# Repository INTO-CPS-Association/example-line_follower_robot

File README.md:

# Line Follower Robot

## Overview
This example was originally developed in the DESTECS project. The model simulates a robot that can follow a line painted on the ground. The line contrasts from the background and the robot uses a number of sensors to detect light and dark areas on the ground. The robot has two wheels, each powered by individual motors to enable the robot to make controlled changes in direction. The number and position of the sensors may be configured in the model. A controller takes input from the sensors and encoders from the wheels to make outputs to the motors.

The robot moves through a number of phases as it follows a line. At the start of each line is a specific pattern that will be known in advance. Once a genuine line is detected on the ground, the robot follows it until it detects that the end of the line has been reached, when it should go to an idle state.

## Supported Features
This study supports the following INTO-CPS technologies:

* Multi-CT model
* 20-Sim (for FMU)
* OpenModelica (for FMU)
* VDM-RT (for FMU)
* INTO-CPS SysML  
* Co-simulation Engine (COE)
* Design Space Exploration
* Test Automation
* Model Checking
* Code Generation

## Additional Information
Additional Information about this case study can be found in the [Examples Compendium](http://projects.au.dk/fileadmin/D3.5_Examples_Compendium_2.pdf#page=34)

Alternatively, contact the case study owner, [Carl Gamble](mailto:carl.gamble@ncl.ac.uk).

Requires DSE scipts 0.3.0 or above

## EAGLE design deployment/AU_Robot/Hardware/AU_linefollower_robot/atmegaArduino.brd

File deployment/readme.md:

# Model Deployment

**Environment**

* bash shell
* Overture FMU exporter https://github.com/overturetool/overture-fmu/releases/download/Release%2F0.2.12/fmu-import-export.jar
* Arduino Software (IDE) https://www.arduino.cc/en/Main/Software 
 * Arduino Mega libraries (included)
* avr-gcc must be avr-gcc (GCC) >= 6.3.0
* avr-g++ must be avr-g++ (GCC) >= 6.3.0
* avr-binutils 2.30
* avr-libc (2.0.0)
* avrdude

On mac: 
* Install Homebrew
* brew install avr-binutils
* brew install avr-gcc
* brew install avr-libc 
* brew install avrdude

(untested avr-gcc upgrade for windows and linux http://blog.zakkemble.co.uk/avr-gcc-builds/)

## Quick guide

This is a all in one guide with minimal explination. It assumes that the tools are nativily installed on a *nix system. You need to provide the path when encoded with `<>`.

You must also have the arduino ide downloaded and locate the sub path within it `hardware/arduino/avr` pointing to the root of the library files which must be provided in the compile script.

Execute the following in the location of the folder containing the shell script: `deploy-backend-mega.sh`

```bash
# Download Overture FMU exporter
wget https://github.com/overturetool/overture-fmu/releases/download/Release%2F0.2.12/fmu-import-export.jar
# Export model
java -jar fmu-import-export.jar -export source -name lf -output . -root <path to model root where *.vdmrt files are located>
# Compile and upload to target
port=/dev/<serial device name> avr=<path to avr in arduino ide> ./deploy-backend-mega.sh lf.fmu
```

## Model Export to C code

To export the model we need to know its location (`root` is the path to the root of the VDM model), and then call the exporter as follows:

```bash
java -jar fmu-import-export.jar -export source -name lf -output . -root LFRController
```

The result is a new file named `lf.fmu` which is a zip archieve that contains the C source code.

## Compliation

Please set the following if not installed in the path:
* `avr` to the location of the avr libraries in the Arduino IDE. For macOS this is:

```bash
avr=/Applications/Arduino.app/Contents/Java/hardware/arduino/avr
```
* set `port` to the path to the serial port of the Arduino Mega
* `avrbin` to `/Applications/Arduino.app/Contents/Java/hardware/tools/avr/bin/`

To compile and deploy the source code FMU call the deploy script as follows (`lf.fmu` is what is previously exported):

```bash
port=/dev/cu.usbmodem1421 avr=/Applications/Arduino.app/Contents/Java/hardware/arduino/avr ./deploy-backend-mega.sh lf.fmu 
```

The output should show something similar to this for the compilation:

```bash

AVR Memory Usage
----------------
Device: atmega2560

Program:   59460 bytes (22.7% Full)
(.text + .data + .bootloader)

Data:       1514 bytes (18.5% Full)
(.data + .bss + .noinit)

```

and for deployment:

```bash
Deploying...

avrdude: Version 6.3, compiled on Jan 17 2017 at 12:01:35
         Copyright (c) 2000-2005 Brian Dean, http://www.bdmicro.com/
         Copyright (c) 2007-2014 Joerg Wunsch

avrdude: AVR device initialized and ready to accept instructions

Reading | ################################################## | 100% 0.01s

avrdude: Device signature = 0x1e9801 (probably m2560)

Writing | ################################################## | 100% 9.55s
Reading | ################################################## | 100% 7.62s

avrdude: verifying ...
avrdude: 59460 bytes of flash verified

avrdude: safemode: hfuse reads as D8
avrdude: safemode: efuse reads as FD
avrdude: safemode: Fuses OK (E:FD, H:D8, L:FF)

avrdude done.  Thank you.

```

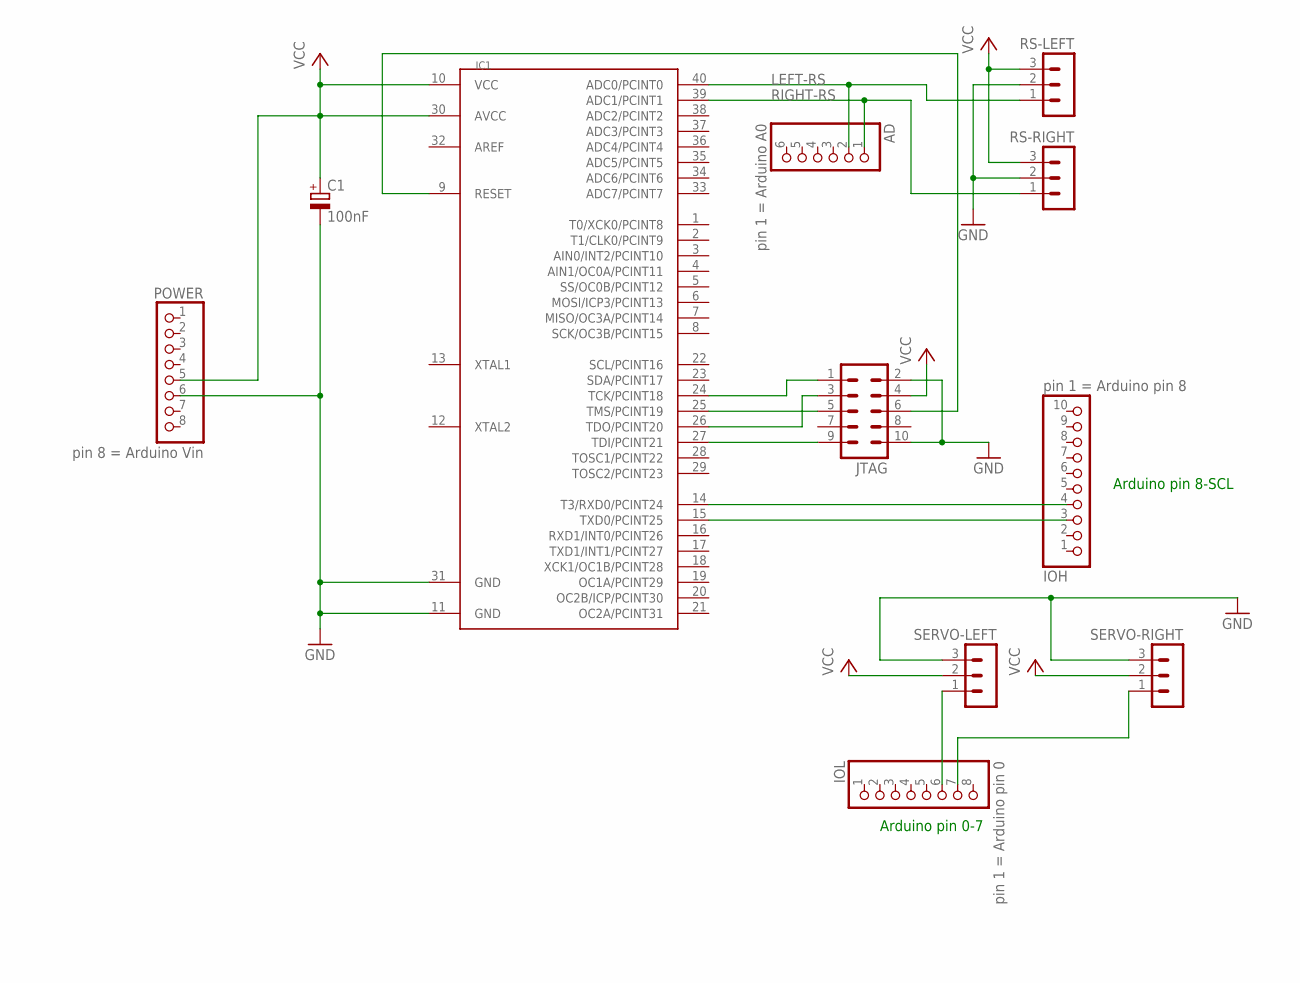
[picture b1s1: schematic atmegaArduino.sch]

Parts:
AD: pin 1 = Arduino A0; 1X06/90
C1: 100nF; E1,8-4
IC1: MEGA1284P; DIL40
IOH: pin 1 = Arduino pin 8; 1X10/90
IOL: pin 1 = Arduino pin 0; 1X08/90
JTAG: ML10L
POWER: pin 8 = Arduino Vin; 1X08/90
RS-LEFT: MA03-1
RS-RIGHT: MA03-1
SERVO-LEFT: MA03-1
SERVO-RIGHT: MA03-1

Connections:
GND: C1.-, IC1.11 (GND), IC1.31 (GND), JTAG.2, JTAG.10, POWER.6, RS-LEFT.2, RS-RIGHT.2, SERVO-LEFT.3, SERVO-RIGHT.3
LEFT-RS: AD.2, IC1.40 (ADC0/PCINT0), RS-LEFT.1
unnamed: IC1.15 (TXD0/PCINT25), IOH.3
unnamed: IC1.14 (T3/RXD0/PCINT24), IOH.4
unnamed: IC1.24 (TCK/PCINT18), JTAG.1
unnamed: IC1.26 (TDO/PCINT20), JTAG.3
unnamed: IC1.27 (TDI/PCINT21), JTAG.9
unnamed: IOL.7, SERVO-RIGHT.1
unnamed: IC1.25 (TMS/PCINT19), JTAG.5
unnamed: IOL.6, SERVO-LEFT.1
unnamed: IC1.9 (RESET), JTAG.6
RIGHT-RS: AD.1, IC1.39 (ADC1/PCINT1), RS-RIGHT.1
VCC: C1.+, IC1.30 (AVCC), JTAG.4, POWER.5, RS-LEFT.3, RS-RIGHT.3, SERVO-LEFT.2, SERVO-RIGHT.2

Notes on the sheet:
Arduino pin 0-7
Arduino pin 8-SCL

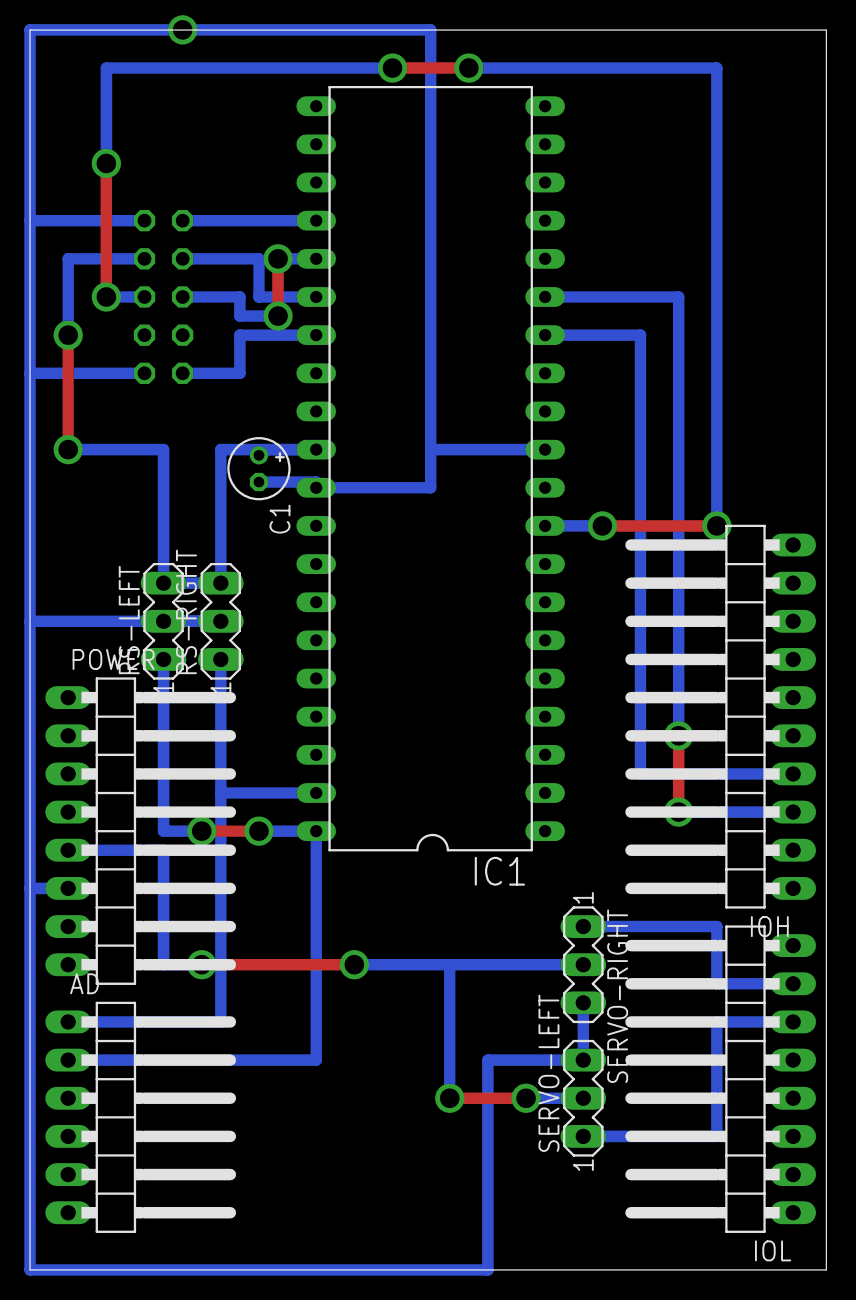
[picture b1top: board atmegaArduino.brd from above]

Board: 2 copper layers, 53.0 x 82.5 mm, 11 parts (1 on the bottom side), 13 nets.

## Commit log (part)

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2017-06-22 autocommit
2017-06-22 updated schematics
2017-06-22 added ardurino code
2017-06-22 updated arduino sw
2017-06-23 UART-specific files.
2017-06-23 updated source code for arduino and schema
2017-06-26 Updates.
2017-06-26 Merging material for Arduino side of things.
2017-06-26 Renaming FMUs so that hyphens don't appear in file names.
2017-06-29 UART code.
2017-06-29 Deployment script WIP.
2017-06-29 Main template file for deployment script.
2017-06-29 Deployment script update.
2017-07-03 Deployment script sans upload command.
2017-07-03 Adding deployment folder.
2017-07-03 Generated file update.
2017-07-03 File cleanup.
2017-07-04 added robot hardware description
2017-07-04 Cleanup after AVR Studio.
2017-07-04 git moved files
2017-07-04 removed
2017-07-04 Update to Arduino part of controller.
2017-07-04 Updated 20-sim
2017-07-05 removed all none essential code
2017-07-05 Updated 3D model
2017-07-05 Removing control loop delay.
2017-07-05 updated deploy script
2017-07-05 Added three maps and multi-models
2017-07-05 cleanup
2017-07-05 Moving sensor threshold value as parameter in hardware interface.
2017-07-05 Tool wrapper FMU update.
2017-07-05 Adding cross-compiled Body.fmu
2017-07-05 Updates for threshold paramameter.
2017-07-05 Account for control thread period.
2017-07-06 FMUs compiled for Linux.
2017-07-06 Updates for thread period.
2017-07-07 Adding DSE scripts
2017-07-07 Recompiled sensors to work on Mac
2017-07-07 Renaming DSE scripts
2017-07-27 Modifying Traceability database for Traceability testing reasons
2017-08-08 add SUT implementation and test model into repository
2017-08-21 FMU updates.
2017-08-21 Source code FMU update.
2017-08-28 Update to source code FMU of VDM controller.
2017-09-19 Standalone controller FMU update.
2017-10-05 Test edit
2017-10-12 Modelio Automatic Commit
2017-10-12 push everything
2017-10-13 Generate model description
2017-10-13 deploy latest Modelio modules
    Deploy latest version (1.3.03) of INTOCPS Modelio extension
2017-10-13 clean
2017-10-13 Generate DSE configuration
2017-10-13 Generate Co simulation configuration
2017-11-12 Updated README and supporting image
2017-11-12 Typo fixed.
2017-11-13 added new mode and i2c communication
2017-11-16 [20-sim 4C] Add the INTO-CPS Line Follower template for 20-sim 4C
2017-11-22 removed serial print from interrupt handler call
2018-01-02 added new 3d design
2018-01-02 added hardware description
2018-01-05 Added new LFRController, Changed CPU freq Changed periodic, Created new multimodel and coe configs
2018-01-05 Reverted cpu freq
2018-01-05 Conducted additional tests
2018-01-05 Updated LFRController to have a periodic thread with 0.5 seconds
2018-01-05 Created additional mm and cosim config
2018-01-12 Added new LFRController and updated the coe.json file
2018-01-12 Updated LFRController to resemble the old example. Created new simulations with stop time of 20
2018-01-12 Updated branch info
2018-01-23 added zero crossing constraints to the variable step multi model and a plotting script
2018-02-13 Updated case study
2018-03-01 line follower example - old simulation results removed, 81 sensor position DSE config added again, laptime objective script uses new DSE 0.3.x exception codes
2018-03-02 old results deleted, objective scripts updated
2018-04-04 Remove .config and .runtime
    Remove Model .runtime and .config folders
2018-04-04 Clean Modelio extensions
    Add and remove latest Modelio extensions
2018-04-17 Modelio migration
    Migrates Modelio project from Modelio 3.4.1 to Modelio 3.7.1
2018-04-25 added new arduino mega deployment
    updated readme
    removed bad line
    updated versions of gcc
    Updated readme with mac info
    updated readme
    added video
2018-04-27 added robot test
2018-04-27 added robot platform description
2018-04-27 added sensor mount height
2018-04-28 added wirring
2018-04-28 switched images
2018-04-28 added sensor mount stl
2018-11-07 Fixes #2
2018-11-21 Re-exported LFR Controller
2018-11-27 Updated hardware desc with links
    Updated hardware desc with links
2019-01-09 added arduino mega sensor shield
2019-08-21 first version of semi-autonomous
2020-01-17 added broadcast messages over serial3
2021-01-29 updated user metric scripts to work with python 3
